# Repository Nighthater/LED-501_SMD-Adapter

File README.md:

# LED-501 SMD Adapter
Adapter Mount for the LED-501 mount from Instrument Systems  

Fit any SMD LED or other Parts onto this mount

## Parts Needed:
- 3D Printer (To Manufacture the Adapter and Assembly Tools, any 3D Print service does the job)
- 2x Standard 2.54mm Female 01x02 Pin Headers 
- 2x Standard 2.54mm Male 01x02 Pin Headers
- PCBs
- SMD LEDs
- 5mm THT LED (Serves as adapter for the LED-501 mount)
- Flat Side cutter (Knipex 78 61 125 or similar)
- Superglue
- Soldering Iron for Headers
- Hot Air Station for SMD LEDs

## Custom PCBs
If you want to test other SMD LEDs than the included 2835 footprint, you can create your own LED Board.
Doing this is simple and can be done in any EDA Software within minutes.

#### Specifications
- The PCB Outline is a 25mm Circle.
- The LED is placed in the exact centre of the circle.
- The Header pins are placed +/- 8.5mm from the Centre.
- Make sure the GND and VCC contacts are each on the same side as the Base PCB. (e.g. GND Both Left, VCC Both Right) You can swap polarities by roating the PCB.

## Assembly

#### Printing Instructions

All parts, except the Adapter (010) can be printed directly without supports.
Be sure to enable rectangular supports for the Adapter.

If you cannot get a somewhat even surface for the PCB to sit on after removing the supports, try angling the adapter 45°, print at a low layerheight (< 0.12 mm) and use a raft and supports (Increase the threshold angle!) for adhesion.

#### Bottom PCB

- Take The Round Assembly Tool Spacer (100) and place the PCB into the Marked Section onto the Assembly Tool.
- Use the PCB Holder (110) to fix the PCB in place
- Insert the 5mm LED and fix it in place using the LED Holder Guide (120), then place and fix the LED with the holder (130)
- Solder the LED in place
- Remove the Assembly Tools
- Use a flat side cutter (Knipex 78 61 125 or similar) to cut off the top LED portion   
- Place the PCB into the Heaxagonal Tool (200)
- Insert the Female 2.54mm 1x2 headers 
- The Headers should face in the opposite direction from the Leads (The LED Leads go upwards, the Headers downwards)
- Place the Assembly upside down onto a flat surface, the headers are now aligned
- Solder the Headers onto the PCB
- Glue the PCB into the Adapter Part (010)   
- Glue the Front cover (020) onto the Adapter
- To protect the LED Leads from damage, you can use the Contact Cover (030)

#### Top PCB

- Solder your SMD LED onto the Top PCB
- Insert the Male 2.54mm 1x2 headers facing away from the SMD LED
- Put the PCB with the headers into the Base PCB, ensuring that the contacts are aligned
- Solder the Headers

The Adapter is now finished and ready for use

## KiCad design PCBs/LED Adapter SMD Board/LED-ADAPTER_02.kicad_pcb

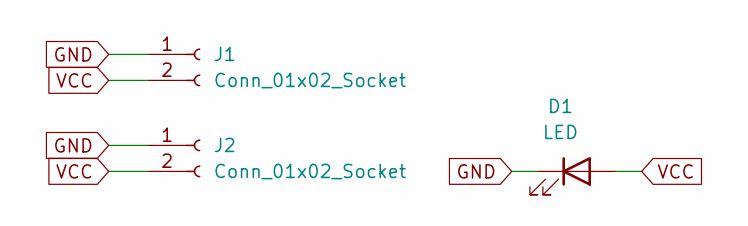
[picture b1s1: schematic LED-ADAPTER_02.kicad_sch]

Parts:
D1: LED; LED_PLCC_2835
J1, J2: Conn_01x02_Socket; PinSocket_1x02_P2.54mm_Vertical

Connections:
GND: D1.1 (K), J1.1, J2.1
VCC: D1.2 (A), J1.2, J2.2

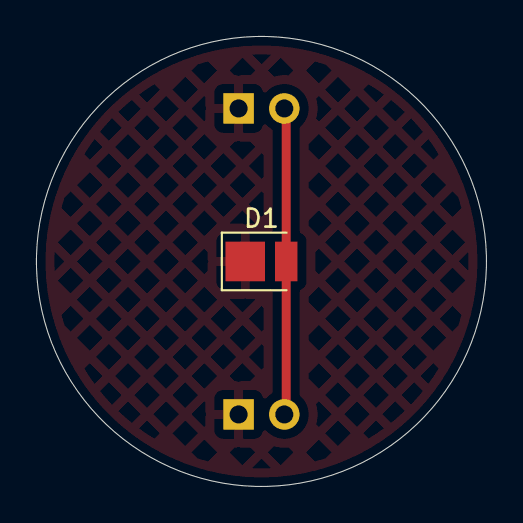
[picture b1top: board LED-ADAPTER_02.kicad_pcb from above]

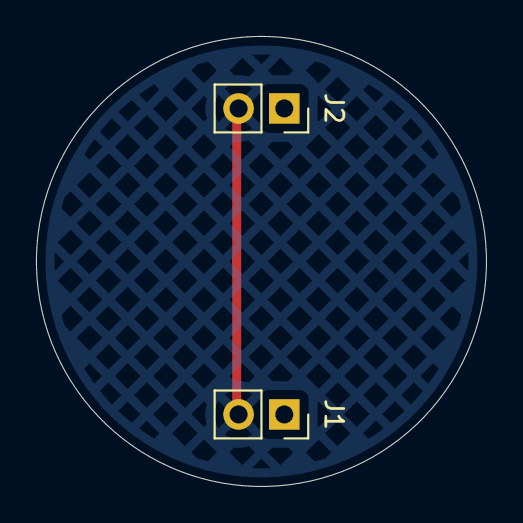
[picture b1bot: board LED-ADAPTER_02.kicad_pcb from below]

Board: 2 copper layers, 25.0 x 25.0 mm, 3 parts (2 on the bottom side), 2 nets.

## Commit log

2025-04-02 Added PCBs
2025-04-02 Add 3D Printed Adapter
2025-04-17 Added Assembly Tools
2025-04-17 Refitted Adapter
2025-05-05 3D Printed Parts
2025-05-06 Create LICENSE
2025-05-22 Added Image
2025-05-23 Added PCB Image
2025-05-23 Fixed Orientations
2025-05-23 Renamed Files
